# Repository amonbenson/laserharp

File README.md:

## Development Setup

### Backend

Setup a virtual environment and install the dependencies:

```bash
python3 -m venv .venv --system-site-packages
source .venv/bin/activate
pip install -r requirements.txt
```

Run the server in development mode:

```bash
source .venv/bin/activate
python -m laserharp.server
```

### Frontend

Install node js and yarn:

```bash
wget -qO- https://raw.githubusercontent.com/nvm-sh/nvm/v0.40.1/install.sh | bash
nvm install --lts
nvm use --lts
npm install -g yarn
```

Install all dependencies:

```bash
cd frontend
yarn install
```

Run the development server:

```bash
yarn dev
```

## Raspberry Pi Performance Improvements:

see https://wiki.linuxaudio.org/wiki/raspberrypi

```bash
for cpu in /sys/devices/system/cpu/cpu[0-9]*; do echo -n performance \
| sudo tee $cpu/cpufreq/scaling_governor; done
```

## Raspberry Pi Reduce Power Consumption

see
https://www.jeffgeerling.com/blog/2023/reducing-raspberry-pi-5s-power-consumption-140x

```bash
# sudo rpi-eeprom-config -e
[all]
BOOT_UART=1
WAKE_ON_GPIO=0
POWER_OFF_ON_HALT=1
```

## Midi uart

- do a `rpi-update` to get the latest kernel firmware
- add to `/boot/firmware/config.txt`:

```
dtoverlay=uart2-pi5
dtoverlay=midi-uart2-pi5
```

## Power via GPIO header

http://blog.dddac.com/wp-content/uploads/Flash-RPi5-and-adding-5000mA-Line-tutorial.pdf

## Allow current user to shutdown

```bash
sudo chmod u+s /sbin/poweroff /sbin/reboot /sbin/shutdown
```

## Diode to Note Mapping

- Root note: C3 (midi note 48, one octave below middle C)
- Global transpose setting

- Modes:
  - **Pedal Harp**: For each note, choose one of:
    - flat
    - natural
    - sharp
  - **Custom Scale**:
    - each diode can be assigned to a specific midi note

- The harp is divided into three horizontal sections resulting in 3 different
  octave ranges

## Transmitted MIDI Messages

:heavy_check_mark: &ndash; Implemented<br> :x: &ndash; Not implemented

### Note On :heavy_check_mark:

```
Laserharp -> Host: 0x90 <note> <velocity>
```

Sent when a laser is intercepted. The note value is determined by the diode and
section that was intercepted. The velocity is fixed at 127.

### Note Off :heavy_check_mark:

```
Laserharp -> Host: 0x80 <note> <velocity>
```

Sent immediately after a laser was plucked. The velocity is fixed at 127.

### Pitch Bend :x:

```
Laserharp -> Host: 0xe0 <pitch_bend_msb> <pitch_bend_lsb>
```

Sent during interception when the hand is moved along the laser beam.

## Received MIDI Messages

:heavy_check_mark: &ndash; Implemented<br> :x: &ndash; Not implemented

### Set Laser Brightness Directly (Note On / Note Off) :heavy_check_mark: (set all lasers :x:)

```
Host -> Laserharp: 0x80 <note> <velocity>
```

Turn off the laser corresponding to the note. A note value of 127 will turn off
all lasers at once.

```
Host -> Laserharp: 0x90 <note> <velocity>
```

Turn on the laser corresponding to the note. A note value of 127 will turn on
all lasers at once. The velocity determines the brightness of the laser.

The brightness is restored automatically after 1s. Note that interceptions will
not be detected when the laser is turned off or too dim.

### Restore Laser Brightness (CC 102) :heavy_check_mark:

```
Host -> Laserharp: 0xb0 102 <value>
```

Restores the laser brightness to the previous value immediately. Value must be
&ge; 64.

### Set Unplucked Laser Brightness (CC 103) :heavy_check_mark:

```
Host -> Laserharp: 0xb0 103 <brightness>
```

Set the brightness for unplucked lasers.

### Set Plucked Laser Brightness (CC 104) :heavy_check_mark:

```
Host -> Laserharp: 0xb0 104 <brightness>
```

Set the brightness when a laser is plucked.

### Set Muted Laser Brightness (CC 105) :heavy_check_mark:

```
Host -> Laserharp: 0xb0 105 <brightness>
```

Sets the brightness when a laser is muted.

### Set Pedal Position And Mutes (CC 110 - 116) :heavy_check_mark:

```
Host -> Laserharp: 0xb0 <pedal_cc> <position>
```

Sets the position and mute of a pedal. The pedals are mapped as follows:

- CC 110 &ndash; C pedal
- CC 111 &ndash; D pedal
- CC 112 &ndash; E pedal
- CC 113 &ndash; F pedal
- CC 114 &ndash; G pedal
- CC 115 &ndash; A pedal
- CC 116 &ndash; B pedal

The value is divided into the ranges:

- 0 &ndash; 31 &ndash; muted
- 32 &ndash; 63 &ndash; lower position (sharp)
- 64 &ndash; 95 &ndash; middle position (natural)
- 96 &ndash; 127 &ndash; upper position (flat)

## IPC Protocol

:heavy_check_mark: &ndash; Implemented<br> :x: &ndash; Not implemented

### USB Midi :x:

```
Bidirectional: 0x0N <byte0> <byte1> <byte2>
```

These packets are equivalent to the USB Midi Protocol with `CN = 1`.

### Din Midi :x:

```
Bidirectional: 0x1N <byte0> <byte1> <byte2>
```

_Note: With the current version, Din Midi is handled directly by the Raspberry
Pi, so this message won't be used._

These packets are equivalent to the USB Midi Protocol with `CN = 1`.

### Set Brightness of a Single Laser :heavy_check_mark:

```
RPi -> STM: 0x80 <diode_index> <brightness> <fade_duration>
```

Set the brightness of a single laser diode. The fade duration is given in tenths
of a second. E.g. a value of 20 will fade the laser to the new brightness over 2
seconds. A duration of 0 will set the brightness immediately.

### Set Brightness of All Lasers :heavy_check_mark:

```
RPi -> STM: 0x81 <brightness> <fade_duration> <unused>
```

Set the brightness of all laser diodes. The fade duration is given in tenths of
a second. E.g. a value of 20 will fade the lasers to the new brightness over 2
seconds. A duration of 0 will set the brightness immediately.

### Get Brightness of a Single Laser :heavy_check_mark:

```
RPi -> STM: 0x82 <diode_index> <unused> <unused>
STM -> RPi: 0x82 <diode_index> <brightness> <unused>
```

### Play Animation :heavy_check_mark:

```
RPi -> STM: 0x83 <animation_id> <duration> <follow_action>
```

Play one of the predefined animations.

**Animation Ids**:<br> 0 &ndash; **Boot animation** &ndash; Played during
powerup of the Raspberry Pi<br> 1 &ndash; **Flip animation** &ndash; Played when
flipping the harp view<br> 2 &ndash; **Test animation** &ndash; Used for
internal testing, alternates between diodes 4 and 5

**Duration**: Given in tenths of a second. E.g. a value of 20 will play the
animation for 2 seconds.

**Follow Actions**:<br> 0 &ndash; **Loop** &ndash; Loop the animation
indefinitely<br> 1 &ndash; **Freeze** &ndash; Play the animation once and stop
on the last frame<br> 2 &ndash; **Off** &ndash; Play the animation once and stop
with all lasers off<br> 3 &ndash; **Restore** &ndash; Play the animation once
and restore the laser brightnesses

### Stop Animation :heavy_check_mark:

```
RPi -> STM: 0x84 <unused> <unused> <unused>
```

Stop the current animation from playing and execute the follow action
immediately. If the follow action was set to 0 (loop indefinitely), the
animation will stop and the lasers will remain in their current state.

### Calibration Button Pressed :heavy_check_mark:

```
STM -> RPi: 0x90 <state_0> <state_1> <state_2>
```

Sent when the calibration button is pressed. The states are given as follows: 0
&ndash; released<br> 1 &ndash; short press<br> 2 &ndash; long press

For example, if the button is short-pressed, then long-pressed, and then
released, the states will be `0x01 0x02 0x00`.

### Get Voltage :heavy_check_mark:

```
RPi -> STM: 0x91 <00> <unused> <unused>
STM -> RPi: 0x91 <00> <voltage_int> <voltage_frac>
```

Returns the current voltage. Currently only the Laser Diode voltage (index 0)
can be measured. The result is given as a decimal number with a resolution of
0.01V and can be calculated as follows:

```python
voltage = voltage_int + voltage_frac / 100
```

### Firmware Version Inquiry :heavy_check_mark:

```
RPi -> STM: 0xf0 <unused> <unused> <unused>
STM -> RPi: 0xf0 <major> <minor> <patch>
```

### Reboot STM :heavy_check_mark:

```
RPi -> STM: 0xf1 <unused> <unused> <unused>
```

### Enter Standby :heavy_check_mark:

```
RPi -> STM: 0xf2 <fade_delay> <fade_duration> <unused>
```

Starts by playing the boot animation, waits for the fade delay, and then fades
the lasers to black over the fade duration. Both delay and duration are given in
tenths of a second.

**Important: This is intended to be used when the harp is turned off. It will
block any further IPC commands and the STM will not respond until it is power
cycled.**

## TODO Software

### Pedal Mutes

- Each Pedal Switch should have a "mute" button. If a string is muted, its
  corresponding laser will be turned on very dimly and no sound will be produced
  for that string.

### Direct Laser Control

- The brightness of each laser should be directly controllable via Note On
  Messages.
- Velocity 1 will map to 0% brightness, velocity 127 will map to 100%
  brightness.
- Velocity 0 / Note Off will return to normal operation and use the internally
  calculated laser brightness
- If a laser is currently in "normal operation" mode, the color will be
  determined by the "unplucked", "plucked", and "muted" brightness settings.

### Section Mode / Section Transpose (formally Section Octave Spacing)

- Sections can be set to different modes.
  - Off &ndash; There are no different sections. Each laser will produce a
    single note.
  - Alterate &ndash; The upper section will play one semitone higher while the
    lower section will play one semitone lower.
  - Single Octave &ndash; The upper section will play one octave higher while
    the lower section will play one octave lower.
  - Double Octave &ndash; The upper section will play two octaves higher while
    the lower section will play two octaves lower.
- Internally, the section mode is stored as a number of semitones.
- This should also be controllable via a Control Change Message

### Global Transpose

- Instead of setting the root note, a fixed root note (e.g. C3) will be used and
  a global transpose setting will offset that root note.

### Direct Pedal/Mute Control

- Using Control Change Messages, the pedal position and mutes can be controlled.

### Predefined Scales

- Each predefined scale controls the pedal positions and mutes for each note.
- Can be selected using Bank Change Messages (CC 0).
- Additional custom scales can be defined and stored internally.

- For each scale, choose:
  - Pitch: `C C# D D# E F F# G G# A A# B`
  - Modes (see https://en.wikipedia.org/wiki/List_of_musical_scales_and_modes):
    - Lydian Dominant &ndash; `1 2 3 #4 5 6 b7`

## MQTT Topics

```
lh/camera/stream
{
    url: "local MJPG stream endpoint"
}

lh/camera/config
{
    shutter_speed: 50000
    iso: 200
}
```

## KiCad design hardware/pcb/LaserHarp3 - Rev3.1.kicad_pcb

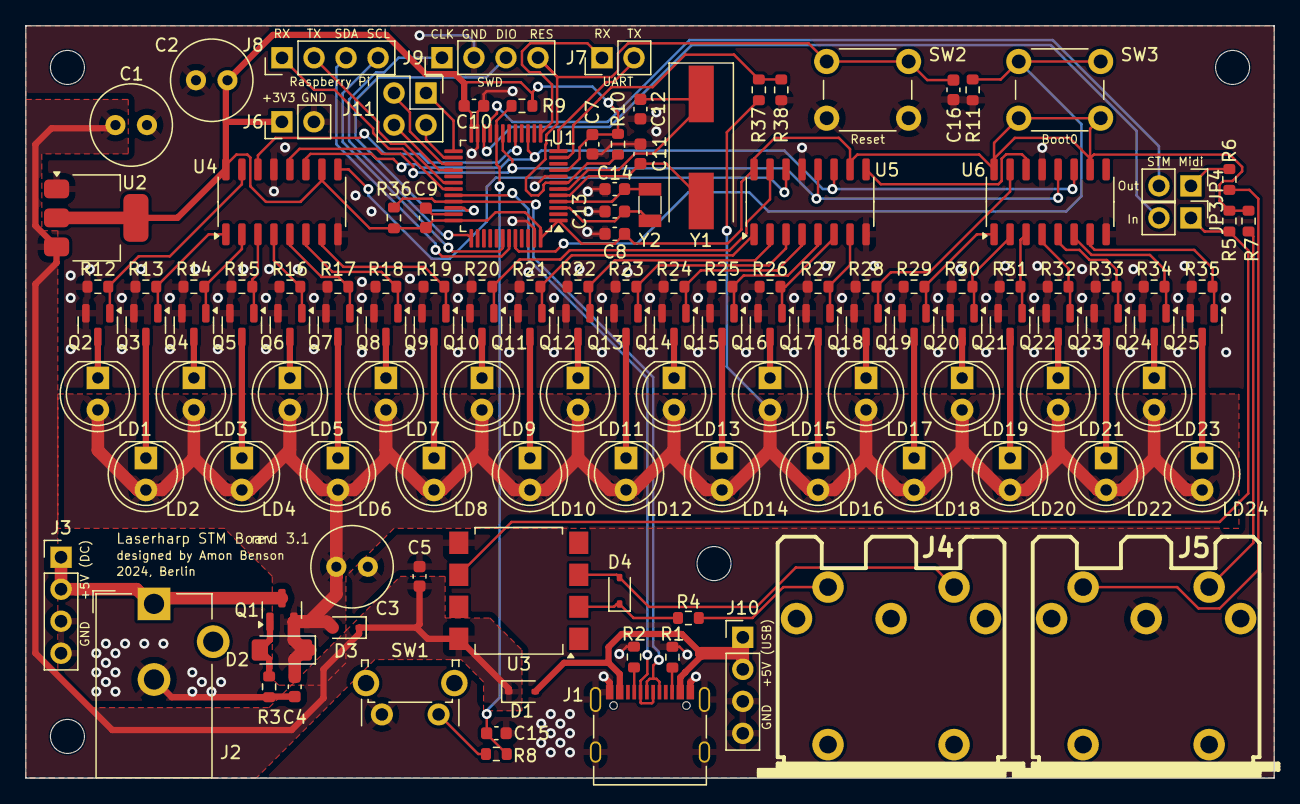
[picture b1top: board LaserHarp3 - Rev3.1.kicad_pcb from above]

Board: 2 copper layers, 99.1 x 59.7 mm, 134 parts (0 on the bottom side), 94 nets.

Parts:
C1, C2: 22u; C_Radial_D6.3mm_H5.0mm_P2.50mm
C3: 10u; C_Radial_D6.3mm_H5.0mm_P2.50mm
C4, C5, C7, C8, C9, C10, C15, C16: 100n; C_0603_1608Metric
C11, C12, C13, C14: 10p; C_0603_1608Metric
D1, D3: 1N5819; D_SOD-323
D2: ZMM5V6; D_MiniMELF
D4: 1N4148WS; D_SOD-323
H1, H2, H3, H4: MountingHole; MountingHole_2.7mm
J1: USB Type C; USB_C_Receptacle_Palconn_UTC16-G
J2: Power; BarrelJack_CUI_PJ-102AH_Horizontal
J3: VIN Power; PinHeader_1x04_P2.54mm_Vertical
J4: Midi_In; din-5
J5: Midi_Out; din-5
J6: 3V3 Power; PinHeader_1x02_P2.54mm_Vertical
J7: UART; PinHeader_1x02_P2.54mm_Vertical
J8: Raspberry Pi; PinHeader_1x04_P2.54mm_Vertical
J9: Debug; PinHeader_1x04_P2.54mm_Vertical
J10: USB Power; PinHeader_1x04_P2.54mm_Vertical
J11: GPIO; PinHeader_2x02_P2.54mm_Vertical
JP3: STM_Midi_In; PinHeader_1x02_P2.54mm_Vertical
JP4: STM_Midi_Out; PinHeader_1x02_P2.54mm_Vertical
LD1, LD2, LD3, LD4, LD5, LD6, LD7, LD8, LD9, LD10, LD11, LD12, LD13, LD14, LD15, LD16, LD17, LD18, LD19, LD20, LD21, LD22, LD23, LD24: Laser_Diode; LED_D5.0mm
Q1: AO3401A; SOT-23
Q2, Q3, Q4, Q5, Q6, Q7, Q8, Q9, Q10, Q11, Q12, Q13, Q14, Q15, Q16, Q17, Q18, Q19, Q20, Q21, Q22, Q23, Q24, Q25: 2N7002; SOT-23
R1, R2: 5.1k; R_0603_1608Metric
R3, R10, R11: 100k; R_0603_1608Metric
R4: 220; R_0603_1608Metric
R5: 470; R_0603_1608Metric
R6, R7: 47; R_0603_1608Metric
R8: 1k; R_0603_1608Metric
R9, R12, R13, R14, R15, R16, R17, R18, R19, R20, R21, R22, R23, R24, R25, R26, R27, R28, R29, R30, R31, R32, R33, R34, R35: 10k; R_0603_1608Metric
R36: 1.5k; R_0603_1608Metric
R37: 220k; R_0603_1608Metric
R38: 330k; R_0603_1608Metric
SW1: Cal; SW_Tactile_SPST_Angled_PTS645Vx39-2LFS
SW2: Reset; SW_PUSH_6mm
SW3: Boot; SW_PUSH_6mm
U1: STM32F103C8T6; LQFP-48_7x7mm_P0.5mm
U2: AMS1117-3.3; SOT-223-3_TabPin2
U3: 6N137; SSO-8_6.7x9.8mm_P2.54mm_Clearance8mm
U4, U5, U6: 74HC595; SO-16_3.9x9.9mm_P1.27mm
Y1: 8 MHz; Crystal_SMD_HC49-SD
Y2: 32.768 KHz; Crystal_SMD_3215-2Pin_3.2x1.5mm

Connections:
+3V3: C2.1, C7.1, C8.1, C9.1, C10.1, J6.1, R5.1, R7.2, R9.1, R10.1, R36.1, SW3.2, U1.1 (VBAT), U1.9 (VDDA), U1.24 (VDD), U1.36 (VDD), U1.48 (VDD), U2.2 (VO), U4.10 (~SRCLR), U4.16 (VCC), U5.10 (~SRCLR), U5.16 (VCC), U6.10 (~SRCLR), U6.16 (VCC)
+5V: C1.1, C5.1, D1.1 (K), D3.1 (K), U2.3 (VI), U3.8 (VCC)
+5VP: C3.1, C4.1, D2.1 (K), D3.2 (A), LD1.2 (A), LD2.2 (A), LD3.2 (A), LD4.2 (A), LD5.2 (A), LD6.2 (A), LD7.2 (A), LD8.2 (A), LD9.2 (A), LD10.2 (A), LD11.2 (A), LD12.2 (A), LD13.2 (A), LD14.2 (A), LD15.2 (A), LD16.2 (A), LD17.2 (A), LD18.2 (A), LD19.2 (A), LD20.2 (A), LD21.2 (A), LD22.2 (A), LD23.2 (A), LD24.2 (A), Q1.2 (S), R37.1
/DAR_DI0: Q2.1 (G), R12.1, U4.15 (QA)
/DAR_DI1: Q3.1 (G), R13.1, U4.1 (QB)
/DAR_DI2: Q4.1 (G), R14.1, U4.2 (QC)
/DAR_DI3: Q5.1 (G), R15.1, U4.3 (QD)
/DAR_DI4: Q6.1 (G), R16.1, U4.4 (QE)
/DAR_DI5: Q7.1 (G), R17.1, U4.5 (QF)
/DAR_DI6: Q8.1 (G), R18.1, U4.6 (QG)
/DAR_DI7: Q9.1 (G), R19.1, U4.7 (QH)
/DAR_DI8: Q10.1 (G), R20.1, U5.15 (QA)
/DAR_DI9: Q11.1 (G), R21.1, U5.1 (QB)
/DAR_DI10: Q12.1 (G), R22.1, U5.2 (QC)
/DAR_DI11: Q13.1 (G), R23.1, U5.3 (QD)
/DAR_DI12: Q14.1 (G), R24.1, U5.4 (QE)
/DAR_DI13: Q15.1 (G), R25.1, U5.5 (QF)
/DAR_DI14: Q16.1 (G), R26.1, U5.6 (QG)
/DAR_DI15: Q17.1 (G), R27.1, U5.7 (QH)
/DAR_DI16: Q18.1 (G), R28.1, U6.15 (QA)
/DAR_DI17: Q19.1 (G), R29.1, U6.1 (QB)
/DAR_DI18: Q20.1 (G), R30.1, U6.2 (QC)
/DAR_DI19: Q21.1 (G), R31.1, U6.3 (QD)
/DAR_DI20: Q22.1 (G), R32.1, U6.4 (QE)
/DAR_DI21: Q23.1 (G), R33.1, U6.5 (QF)
/DAR_DI22: Q24.1 (G), R34.1, U6.6 (QG)
/DAR_DI23: Q25.1 (G), R35.1, U6.7 (QH)
/Diode Array/DO0: LD1.1 (C), Q2.3 (D)
/Diode Array/DO1: LD2.1 (C), Q3.3 (D)
/Diode Array/DO2: LD3.1 (C), Q4.3 (D)
/Diode Array/DO3: LD4.1 (C), Q5.3 (D)
/Diode Array/DO4: LD5.1 (C), Q6.3 (D)
/Diode Array/DO5: LD6.1 (C), Q7.3 (D)
/Diode Array/DO6: LD7.1 (C), Q8.3 (D)
/Diode Array/DO7: LD8.1 (C), Q9.3 (D)
/Diode Array/DO8: LD9.1 (C), Q10.3 (D)
/Diode Array/DO9: LD10.1 (C), Q11.3 (D)
/Diode Array/DO10: LD11.1 (C), Q12.3 (D)
/Diode Array/DO11: LD12.1 (C), Q13.3 (D)
/Diode Array/DO12: LD13.1 (C), Q14.3 (D)
/Diode Array/DO13: LD14.1 (C), Q15.3 (D)
/Diode Array/DO14: LD15.1 (C), Q16.3 (D)
/Diode Array/DO15: LD16.1 (C), Q17.3 (D)
/Diode Array/DO16: LD17.1 (C), Q18.3 (D)
/Diode Array/DO17: LD18.1 (C), Q19.3 (D)
/Diode Array/DO18: LD19.1 (C), Q20.3 (D)
/Diode Array/DO19: LD20.1 (C), Q21.3 (D)
/Diode Array/DO20: LD21.1 (C), Q22.3 (D)
/Diode Array/DO21: LD22.1 (C), Q23.3 (D)
/Diode Array/DO22: LD23.1 (C), Q24.3 (D)
/Diode Array/DO23: LD24.1 (C), Q25.3 (D)
/MIDI_IN_SNK: D4.2 (A), J4.4, U3.3 (C)
/MIDI_IN_SRC: J4.5, R4.1
/MIDI_OUT_SNK: J5.4, R7.1
/MIDI_OUT_SRC: J5.5, R6.1
/USB_PWR: D1.2 (A), J1.A4 (VBUS), J1.A9 (VBUS), J1.B4 (VBUS), J1.B9 (VBUS), J10.1, J10.2
/VIN: J2.1, J3.1, J3.2, Q1.3 (D)
BOOT0: R11.1, SW3.1, U1.44 (BOOT0)
BTN_CAL: C15.1, R8.2, R9.2, U1.20 (PB2)
DEBUG_RX: J7.1, U1.13 (PA3)
DEBUG_TX: J7.2, U1.12 (PA2)
GND: C1.2, C2.2, C3.2, C4.2, C5.2, C7.2, C8.2, C9.2, C10.2, C11.2, C12.2, C13.2, C14.2, C15.2, C16.2, J1.A1 (GND), J1.A12 (GND), J1.B1 (GND), J1.B12 (GND), J1.S1 (SHIELD), J2.2, J3.3, J3.4, J5.2, J6.2, J9.2, J10.3, J10.4, Q2.2 (S), Q3.2 (S), Q4.2 (S), Q5.2 (S), Q6.2 (S), Q7.2 (S), Q8.2 (S), Q9.2 (S), Q10.2 (S), Q11.2 (S), Q12.2 (S), Q13.2 (S), Q14.2 (S), Q15.2 (S), Q16.2 (S), Q17.2 (S), Q18.2 (S), Q19.2 (S), Q20.2 (S), Q21.2 (S), Q22.2 (S), Q23.2 (S), Q24.2 (S), Q25.2 (S), R1.2, R2.2, R3.2, R11.2, R12.2, R13.2, R14.2, R15.2, R16.2, R17.2, R18.2, R19.2, R20.2, R21.2, R22.2, R23.2, R24.2, R25.2, R26.2, R27.2, R28.2, R29.2, R30.2, R31.2, R32.2, R33.2, R34.2, R35.2, R38.2, SW1.2, SW2.1, U1.8 (VSSA), U1.23 (VSS), U1.35 (VSS), U1.47 (VSS), U2.1 (GND), U3.5 (GND), U4.8 (GND), U4.13 (~OE), U5.8 (GND), U5.13 (~OE), U6.8 (GND), U6.13 (~OE)
GPIO_PB12: J11.1, U1.25 (PB12)
GPIO_PB13: J11.2, U1.26 (PB13)
GPIO_PB14: J11.3, U1.27 (PB14)
GPIO_PB15: J11.4, U1.28 (PB15)
LA_VPROBE: R37.2, R38.1, U1.11 (PA1)
MIDI_RX: JP3.2 (B), U1.22 (PB11)
MIDI_TX: JP4.2 (B), U1.21 (PB10)
unnamed: D2.2 (A), Q1.1 (G), R3.1
unnamed: D4.1 (K), R4.2, U3.2 (A)
unnamed: J1.A5 (CC1), R2.1
unnamed: J1.B5 (CC2), R1.1
unnamed: JP3.1 (A), R5.2, U3.6 (VO)
unnamed: JP4.1 (A), R6.2
unnamed: R8.1, SW1.1
unnamed: U4.9 (QH'), U5.14 (SER)
unnamed: U5.9 (QH'), U6.14 (SER)
RASPI_RX: J8.1, U1.31 (PA10)
RASPI_SCL: J8.4, U1.42 (PB6)
RASPI_SDA: J8.3, U1.43 (PB7)
RASPI_TX: J8.2, U1.30 (PA9)
RCC_OSC_IN: C11.1, U1.5 (PD0), Y1.2
RCC_OSC_OUT: C12.1, U1.6 (PD1), Y1.1
RESET: C16.1, J9.4, R10.2, SW2.2, U1.7 (NRST)
SR_CLK: U1.15 (PA5), U4.11 (SRCLK), U5.11 (SRCLK), U6.11 (SRCLK)
SR_DS0: U1.17 (PA7), U4.14 (SER)
SR_LATCH: U1.19 (PB1), U4.12 (RCLK), U5.12 (RCLK), U6.12 (RCLK)
SWCLK: J9.1, U1.37 (PA14)
SWDIO: J9.3, U1.34 (PA13)
USB_D+: J1.A6 (D+), J1.B6 (D+), R36.2, U1.33 (PA12)
USB_D-: J1.A7 (D-), J1.B7 (D-), U1.32 (PA11)
USB_OSC_IN: C13.1, U1.3 (PC14), Y2.2
USB_OSC_OUT: C14.1, U1.4 (PC15), Y2.1

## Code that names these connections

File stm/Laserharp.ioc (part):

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Mcu.Name=STM32F103C(8-B)Tx
Mcu.Package=LQFP48
Mcu.UserName=STM32F103C8Tx
PA1.GPIOParameters=GPIO_Label
PA1.GPIO_Label=LA_VPROBE
PA1.Signal=ADCx_IN1
PA10.GPIOParameters=GPIO_Label
PA10.GPIO_Label=IPC_RX
PA10.Mode=Asynchronous
PA10.Signal=USART1_RX
PA11.Mode=Device
PA11.Signal=USB_DM
PA12.Mode=Device
PA12.Signal=USB_DP
PA13.Mode=Serial_Wire
PA13.Signal=SYS_JTMS-SWDIO
PA14.Mode=Serial_Wire
PA14.Signal=SYS_JTCK-SWCLK
PA2.GPIOParameters=GPIO_Label
PA2.GPIO_Label=DEBUG_TX
PA2.Mode=Asynchronous
PA2.Signal=USART2_TX
PA3.GPIOParameters=GPIO_Label
PA3.GPIO_Label=DEBUG_RX
PA3.Mode=Asynchronous
PA3.Signal=USART2_RX
PA5.GPIOParameters=GPIO_Label
PA5.GPIO_Label=LA_CLK
PA5.Mode=TX_Only_Simplex_Unidirect_Master
PA5.Signal=SPI1_SCK
PA7.GPIOParameters=GPIO_Label
PA7.GPIO_Label=LA_DS
PA7.Mode=TX_Only_Simplex_Unidirect_Master
PA7.Signal=SPI1_MOSI
PA9.GPIOParameters=GPIO_Label
PA9.GPIO_Label=IPC_TX
PA9.Mode=Asynchronous
PA9.Signal=USART1_TX
PB1.GPIOParameters=GPIO_Label
PB1.GPIO_Label=LA_LATCH
PB1.Signal=S_TIM3_CH4
PB10.GPIOParameters=GPIO_Label
PB10.GPIO_Label=DIN_TX
PB10.Mode=Asynchronous
PB10.Signal=USART3_TX
PB11.GPIOParameters=GPIO_Label
PB11.GPIO_Label=DIN_RX
PB11.Mode=Asynchronous
PB11.Signal=USART3_RX
PB2.GPIOParameters=GPIO_Label
PB2.GPIO_Label=BTN_CAL
PB2.Signal=GPIO_Input
PB6.GPIOParameters=GPIO_Label
PB6.GPIO_Label=IPC_SCL
PB6.Mode=I2C
PB6.Signal=I2C1_SCL
PB7.GPIOParameters=GPIO_Label
PB7.GPIO_Label=IPC_SDA
PB7.Mode=I2C
PB7.Signal=I2C1_SDA
PD0-OSC_IN.Mode=HSE-External-Oscillator
PD0-OSC_IN.Signal=RCC_OSC_IN
PD1-OSC_OUT.Mode=HSE-External-Oscillator
PD1-OSC_OUT.Signal=RCC_OSC_OUT
RCC.SYSCLKFreq_VALUE=72000000
RCC.SYSCLKSource=RCC_SYSCLKSOURCE_PLLCLK
board=custom

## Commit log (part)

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2023-10-03 finished implementation of IPC
2023-10-04 added camera test
2023-10-04 added better camera processing
2023-10-04 added basic image processing
2023-10-05 added calibration visualization
2023-10-05 added artwork
2023-10-06 more work on midi handling
2023-10-06 added main event loop
2023-10-06 added some init sequence
2023-10-06 added interception events
2023-10-06 basic processing loop (cam->midi_out->midi_in->lasers) working
2023-10-09 STM -> RPi connection working!
2023-10-09 ipc fully working
2023-10-10 improved serial read performance
2023-10-11 updates to midi IO
2023-10-11 added read timeout andd graceful shutdown
2023-10-11 added stop function to ipc
2023-10-12 added ble midi v1
2023-10-12 added unfinished server version
2023-10-12 moved ble_midi to separate branch
2023-10-12 fixed test runs
2023-10-18 added actual calibration code
2023-10-23 added better calibration sequence, data gets stored to json file
2023-10-24 added new calibration format
2023-10-24 sync with main thread now working
2023-10-25 added global configuration
2023-10-25 bugfixes with the new config system
2023-10-25 added kill script and debugging controls
2023-10-25 added pitch bend functionality
2023-10-26 added new image processor (untested)
2023-10-26 added full test suite for image processor
2023-10-26 changed config keys
2023-10-26 added laser array, changes to test suite
2023-10-26 more updates to config system
2023-10-28 added and tested laser array
2023-10-28 large rework of class system
2023-10-28 renaming
2023-10-28 major update to camera, untested
2023-10-29 reworked camera module
2023-10-29 updates to midi event
2023-10-29 added invalid cable test
2023-10-29 added new calibrator class with tests
2023-10-29 added flag for calibrator debug images
2023-10-29 added load and save functionality to calibrator
2023-10-29 slices now make use of set_all
2023-10-31 added new app code
2023-10-31 app in a semi-working state
2024-08-14 added new installation scripts
2024-08-14 updated venv configuration
2024-08-14 added new serial configurations
2024-08-14 updated library to use new libcamera2
2024-08-14 validated working camera
2024-08-14 added github ci
2024-08-14 added apt prerequisites to ci yaml
2024-08-14 removed libcamera dependency
2024-08-14 moved opencv to pip dependencies
2024-08-14 made camera tests optional
2024-08-14 added custom camera output stream handler
2024-08-14 fixed fps issues
2024-08-14 fixed paths in tests
2024-08-14 added frontend directory
2024-08-14 added tailwind and linting
2024-08-18 added live drawing capabilities
2024-08-18 added frontend camera stream
2024-08-18 added single devserver
2024-08-18 massive updates to backend/frontend connection via websockets
2024-08-19 added mjpg stream
2024-08-19 improved mjpeg stream quality
2024-08-19 added new state management using refs
2024-08-19 added result visualization to webview
2024-08-19 updates to workflow
2024-08-19 fixed lint issues, changed readme and actions
2024-08-19 updated state management on server, fixed bug in beam visualization
2024-08-19 added hardware serial port
2024-08-23 added pylint
2024-08-23 ran pylint
2024-08-23 added pylint code action
2024-08-23 added justfile
2024-08-23 added black formatter
2024-09-04 added hardware files
2024-09-04 added stm files
2024-09-04 added code workspace file
2024-09-04 added rpi subdirectory
2024-09-04 update to gitignore
2024-09-04 updated to workspace configuration, fixed github workflows
2024-09-04 major restructuring of github actions
2024-09-04 more updates to actions
2024-09-04 updated stm workflow
2024-09-04 fixed missing version stuff
2024-09-09 modified testing directory and README badges
2024-09-09 renamed ci workflows
2024-09-09 updated tasks
2024-09-09 stripped stm firmware
2024-09-09 added usb renumeration
2024-09-09 added MIDI usb driver
2024-09-09 verified usb midi in working
2024-09-09 added usb midi send, multiple sends seem to cause a deadlock in certain situations
2024-09-09 it seems that midi rx and tx will need to be separated to different tasks
2024-09-09 updates on usb send
2024-09-10 moved usb code to separate driver
2024-09-10 added ipc driver
2024-09-10 added laserarray
2024-09-11 changes to rpi code
2024-09-11 added stm ipc commands
2024-09-11 updated calibration process
2024-09-15 added more laser diodes, added calibrate button to web ui
2024-09-16 updated folder structure
2024-09-16 fixed testing framework
2024-09-16 fixed ipc tests
2024-09-16 fixed linting scripts
2024-09-16 fixed a lot of linting issues
2024-09-16 fixed more linting issues
2024-09-16 added option to disable hardware specific components
2024-09-16 cleanup unused event classes
2024-09-17 added new perci state management
2024-09-17 added new config system to ipc component
2024-09-17 added new config to din_midi
2024-09-17 added new config to laser_array
2024-09-17 type updates
2024-09-17 added new config system to image processor
2024-09-17 updated all components to use the new config system
2024-09-17 added missing import
2024-09-17 added image calibration state
2024-09-18 updated camera to include a frame tracker
2024-09-18 added new app state synchronization to frontend
2024-09-18 updated state order
2024-09-18 added new calibration view
2024-09-18 added image processor results
2024-09-18 added calibration live view
2024-09-18 fixed issues with calibration
2024-09-18 moved debug view to separate route
2024-09-18 added notes on the midi conversion component
2024-09-18 added settings
2024-09-18 layout updates
2024-09-18 added new intersection visualization on main page
2024-09-18 added differenty colored strings
2024-09-19 fixed test configuration order
2024-09-22 updated to settings
2024-09-22 added section on gpio power
2024-09-22 updates to vscode startup settings and camera view
2024-09-22 added settings, fixes in backend and frontend
2024-09-22 implemented setting update routine
2024-09-22 added more validation to settings api
2024-09-22 added pedal settings, ui updates
2024-09-22 upped camera frame rate to 50 FPS
2024-09-24 removed node_modules from source control
2024-09-24 renamed directories
2024-09-24 more renaming of directories
2024-09-25 updated readme with initial build commands
2024-09-26 settings rework
2024-09-26 added database store
2024-09-28 fixed setting types
2024-09-28 calibration is now stored in the settings file
2024-09-28 added client_writable property
2024-09-29 added tailwind color theme
2024-09-29 added support for plucked beam brightness
2024-09-29 fixed initial laser brightness
2024-09-29 fixed bug in image processor
2024-10-03 added new favicon generator
2024-10-03 added setup.py
2024-10-03 added deployment options
2024-10-03 fixed laserharp service
2024-10-12 added camera fixes for raspberry pi 3
2024-10-15 updates config and home view to work with raspberry pi 5
2024-10-15 updated installer scripts
2024-10-15 updated pcb
2024-10-15 added intro animation
2024-10-15 updated laser brightness in intro animation
2024-10-15 fixed debug view in production app
2024-10-18 added loader icon, changed navbar layout
2024-10-18 fixed width issues on main content
2024-10-18 fixed bug with status indicator
2024-10-18 removed unused loader icon
2024-10-18 added toggleable menu
2024-10-18 added icons, updates to navbar
2024-10-18 updated unplucked beam brightness
2024-10-18 ran yarn lint
2024-10-18 updated github workflows
2024-10-18 added workflow dispatch triggers
2024-10-20 fixed image calibrator tests
2024-10-20 Update badges
2024-10-20 fixed issues with parens in title
2024-10-21 added first fabrication order export
2024-10-21 changes to sheet metal AI project
2024-10-22 updated frontend navbar
2024-10-22 fixed navbar bug in mobile view
2024-10-23 small bugfixes, persisting mjpeg stream issue in firefox
2024-10-23 modified readme md
2024-10-27 added firemware tests
2024-10-27 added get brightness method and updated implemented method list
2024-10-27 updated test speed
2024-10-27 added animation playback engine, untested
2024-10-27 added tests for the animation system
2024-10-27 added calibration button and voltage specs to readme
2024-10-27 renamed midi_converter -> orchestrator
2024-10-27 updated log level to improve processing speed
2024-10-27 updated orchestrator layout
2024-10-27 changed intro animation
2024-10-27 added flipped setting
2024-10-28 updated settings fetch method
2024-10-28 added ui elements to frontend
2024-10-28 added restore follow_action and updated the flip animation
2024-10-28 added flip animation trigger
2024-10-28 fixed flip direction
2024-10-29 implemented laser fading via ipc command
2024-10-29 added tests for laser fading, added fade during startup
2024-10-29 implemented calibration and poweroff button
2024-10-29 implemented standby command in the firmware
2024-10-29 added standby command to app code
2024-10-30 updated standby behaviour
2024-10-30 updates to standby and cal button
2024-10-30 changed non-button sequence character
2024-10-30 changed sequence char once again
2024-10-30 hwbutton working, fixed bug where lasers wouldn't turn off at the start of a calibration
2024-10-30 added button assignment and quick actions to frontend
2024-11-04 removed old hw folder
2024-11-04 added get voltage function
2024-11-04 added test for get_voltage
2024-11-05 updated frontend pedals, added todos to readme
2024-11-05 implemented beam muting
2024-11-05 implemented predefined scales on the server side
2024-11-07 updates to frontend layout
2024-11-07 implemented direct laser control via DIN midi
2024-11-11 fixed camera streaming issues
2024-11-12 ran environment setup
2024-11-12 more updates to installer scripts
2024-11-13 implemented the majority of midi messages
2024-11-13 fixed description in readme
2024-11-20 added jlc3dp ordered parts
2025-03-10 added emulator files
2025-03-10 added arguments
2025-03-10 added frontend
2025-03-12 added docker compose file and redis db
2025-03-12 updated config to match new hardware setup
2025-03-14 added mqtt with scope, but not working atm
2025-03-14 new topic publisher working
2025-03-16 added env load check
2025-03-16 added emulator web ui
2025-03-17 added vscode workspace
2025-03-17 added more linting
2025-03-17 virtual camera feed now working
2025-03-17 added docker laserharp and mqtt client scaffold
2025-03-18 added new component system
2025-03-19 added pubsub and refactored component methods
2025-03-19 updated pubsub with wait_change and wait_any_change methods
2025-03-19 update payload encoding system
2025-03-19 added new mqtt read function
2025-03-19 added new concept of mqtt components
2025-03-19 moved pubsub pattern to separate component
2025-03-19 separated mqtt component classes
2025-03-19 access system rewrite
2025-03-21 added new access restriction system, only somethat usable without ACLs
2025-03-21 validated access on raw pubsub
2025-03-22 added schema validation system
2025-03-22 fixed jsonschema validator initialization
2025-03-22 added configurable calss
2025-03-22 rename pubsub -> endpoint
2025-03-22 added camera, emulated stream not working atm
2025-03-22 changes to mqtt class layout
2025-03-22 updated component root system
2025-03-23 verified capture working
2025-03-23 added emulator class
2025-03-26 started implementing stm board
2025-05-15 added web emulator
2025-05-15 updated frontend api proxy settings
2025-05-15 added venv to install python to
2025-05-15 updates to install script and import info
2025-05-26 added justfile to control install and uninstall commands
2025-05-26 added dynamic iso and shutter speed setting to server
2025-05-26 fixed calibration issues
2025-05-27 added better blob detector
2025-05-27 adjusted fov settings
2025-05-28 added oversampling thread without functionality
2025-05-28 added flipping for the new orchestrator
2025-05-28 added more frame blurring to smooth out beam length
2025-05-28 added kalman filter for camera pixel input
2025-05-28 fixed bug with emulated beam brightness
2025-06-04 implemented calibration using 2nd order polynom
2025-06-04 added cubic calibration method
2025-06-04 fixed bug in calibration and updated configured coverage
2025-06-24 added blackout and midi controls for orchestrator settings
2025-06-26 added threshold as a settings
